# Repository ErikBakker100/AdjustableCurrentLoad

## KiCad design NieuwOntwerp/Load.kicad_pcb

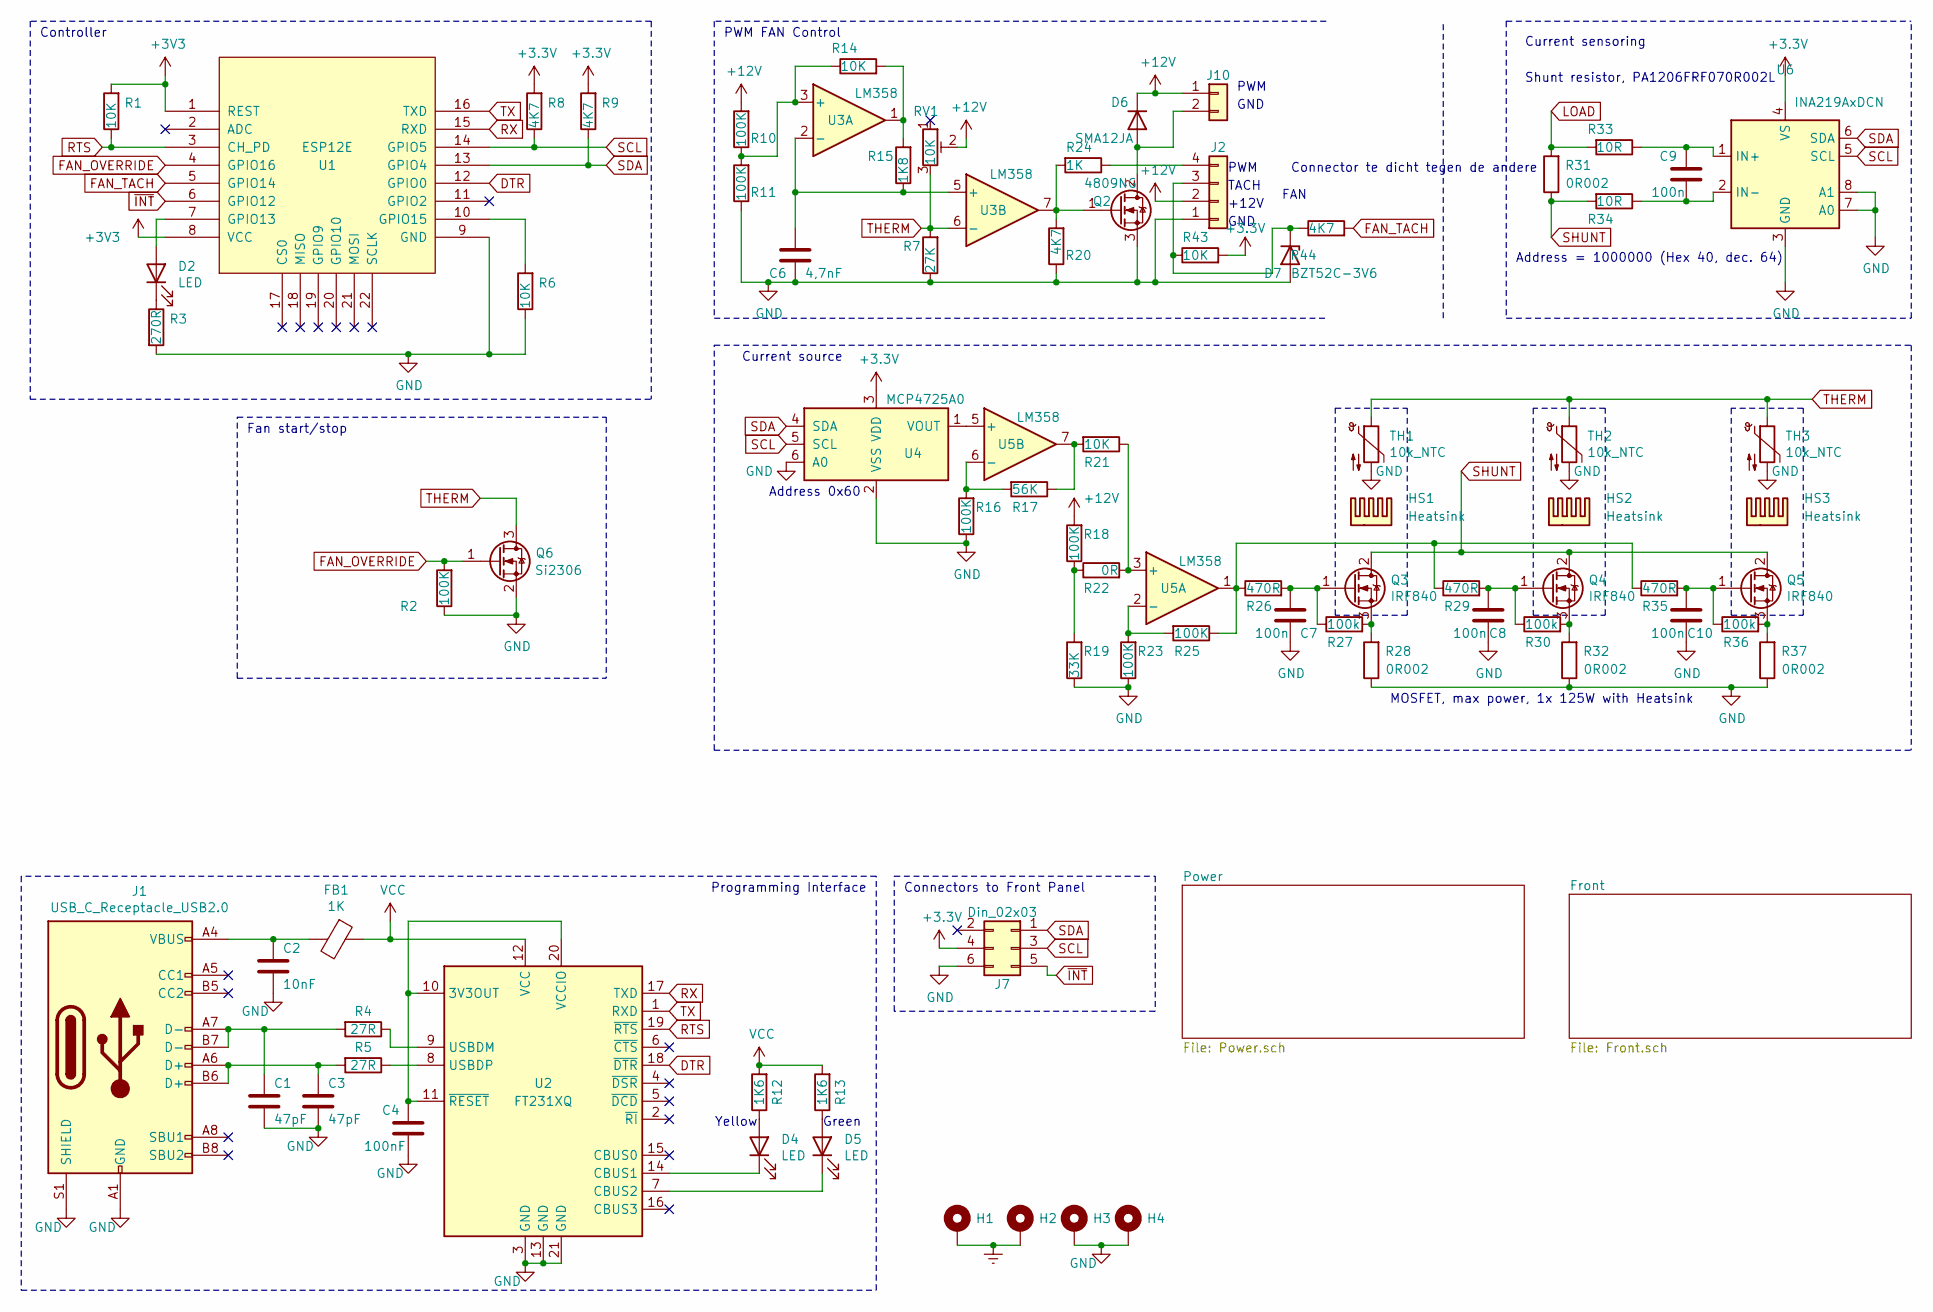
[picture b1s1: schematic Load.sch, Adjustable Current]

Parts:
C1, C3: 47pF; C_0402_1005Metric
C2: 10nF; C_0402_1005Metric
C4: 100nF; C_0603_1608Metric
C6: 4,7nF; C_0402_1005Metric
C7, C8, C9, C10: 100n; C_0603_1608Metric
D2: LED; LED_0603_1608Metric_Pad1.05x0.95mm_HandSolder
D4, D5: LED; LED_0603_1608Metric
D6: SMA12JA; D_SMA
D7: BZT52C-3V6; D_SOD-123
FB1: 1K; R_0603_1608Metric
H1, H2, H3, H4: MountingHole_Pad; MountingHole_3.2mm_M3_DIN965_Pad
HS1, HS2, HS3: Heatsink; Heatsink_TO220
J1: USB_C_Receptacle_USB2.0; USB-C_Receptable_SMD_16pin
J2: Conn_01x02; JST_XH_B4B-XH-A_1x04_P2.50mm_Vertical
J7: Din_02x03; IDC-Header_2x03_P2.54mm_Vertical
J10: Conn_01x02; JST_XH_B2B-XH-AM_1x02_P2.50mm_Vertical
Q2: 4809NG; 369AA
Q3, Q4, Q5: IRF840; TO-220-3_Vertical
Q6: Si2306; SOT-23
R1, R6, R14, R21, R43: 10K; R_0603_1608Metric
R2, R10, R11, R16, R18, R23, R25: 100K; R_0603_1608Metric
R3: 270R; R_0603_1608Metric
R4, R5: 27R; R_0402_1005Metric
R7: 27K; R_0603_1608Metric
R8, R9, R20, R44: 4K7; R_0603_1608Metric
R12, R13: 1K6; R_0603_1608Metric
R15: 1K8; R_0603_1608Metric
R17: 56K; R_0603_1608Metric
R19: 33K; R_0603_1608Metric
R22: 0R; R_0603_1608Metric
R24: 1K; R_0603_1608Metric
R26, R29, R35: 470R; R_0603_1608Metric
R27, R30, R36: 100k; R_0603_1608Metric
R28, R31, R32, R37: 0R002; R_1206_3216Metric
R33, R34: 10R; R_0603_1608Metric
RV1: 10K; Potentiometer_Bourns_3296W_Vertical
TH1, TH2, TH3: 10k_NTC; THERM_NXRT15XH103FA1B040
U1: ESP12E; ESP-12E_SMD
U2: FT231XQ; QFN-20-1EP_4x4mm_P0.5mm_EP2.5x2.5mm
U3, U5: LM358; SOIC-8_3.9x4.9mm_P1.27mm
U4: MCP4725A0; SOT-23-6
U6: INA219AxDCN; SOT-23-8

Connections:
+12V: D6.1 (K), J2.2, J10.1, R10.2, R18.2, RV1.2; also elsewhere on the board
DTR: U1.12 (GPIO0), U2.18 (~DTR)
Earth: H1.1, H2.1; also elsewhere on the board
FAN_OVERRIDE: Q6.1 (G), R2.2, U1.4 (GPIO16)
FAN_TACH: R44.2, U1.5 (GPIO14)
GND: C1.2, C2.2, C3.2, C4.2, C6.1, C7.1, C8.1, C10.1, D7.2 (A), H3.1, H4.1, J1.A1 (GND), J1.A12 (GND), J1.B1 (GND), J1.B12 (GND), J1.S1 (SHIELD), J2.1, J7.6, Q2.3 (S), Q6.2 (S), R2.1, R3.2, R6.1, R7.1, R11.1, R16.1, R19.1, R20.1, R23.1, R28.1, R32.1, R37.1, TH1.2, TH2.2, TH3.2, U1.9 (GND), U2.3 (GND), U2.13 (GND), U2.21 (GND), U4.2 (VSS), U4.6 (A0), U6.3 (GND), U6.7 (A0), U6.8 (A1); also elsewhere on the board
LOAD: R31.2, R33.2; also elsewhere on the board
unnamed: C1.1, J1.A7 (D-), J1.B7 (D-), R4.2
unnamed: C2.1, FB1.2, J1.A4 (VBUS), J1.A9 (VBUS), J1.B4 (VBUS), J1.B9 (VBUS)
unnamed: C3.1, J1.A6 (D+), J1.B6 (D+), R5.2
unnamed: C4.1, U2.10 (3V3OUT), U2.11 (~RESET), U2.20 (VCCIO)
unnamed: C6.2, R15.1, U3.2 (-), U3.5 (+)
unnamed: C7.2, Q3.1 (G), R26.2, R27.1
unnamed: C8.2, Q4.1 (G), R29.2, R30.1
unnamed: C9.1, R33.1, U6.1 (IN+)
unnamed: C9.2, R34.1, U6.2 (IN-)
unnamed: C10.2, Q5.1 (G), R35.2, R36.1
unnamed: D2.1 (K), R3.1
unnamed: D2.2 (A), U1.7 (GPIO13)
unnamed: D4.1 (K), U2.14 (CBUS1)
unnamed: D4.2 (A), R12.1
unnamed: D5.1 (K), U2.7 (CBUS2)
unnamed: D5.2 (A), R13.1
unnamed: D6.2 (A), J10.2, Q2.2 (D)
unnamed: D7.1 (K), J2.3, R43.1, R44.1
unnamed: J2.4, R24.1
unnamed: Q2.1 (G), R20.2, R24.2, U3.7
unnamed: Q3.3 (S), R27.2, R28.2
unnamed: Q4.3 (S), R30.2, R32.2
unnamed: Q5.3 (S), R36.2, R37.2
unnamed: R4.1, U2.9 (USBDM)
unnamed: R5.1, U2.8 (USBDP)
unnamed: R6.2, U1.10 (GPIO15)
unnamed: R10.1, R11.2, R14.1, U3.3 (+)
unnamed: R14.2, R15.2, U3.1
unnamed: R16.2, R17.2, U5.6 (-)
unnamed: R17.1, R21.2, U5.7
unnamed: R18.1, R19.2, R22.1
unnamed: R21.1, R22.2, U5.3 (+)
unnamed: R23.2, R25.2, U5.2 (-)
unnamed: R25.1, R26.1, R29.1, R35.1, U5.1
unnamed: U4.1 (VOUT), U5.5 (+)
RTS: R1.1, U1.3 (CH_PD), U2.19 (~RTS)
RX: U1.15 (RXD), U2.17 (TXD)
SCL: J7.3, R8.1, U1.14 (GPIO5), U4.5 (SCL), U6.5 (SCL)
SDA: J7.1, R9.1, U1.13 (GPIO4), U4.4 (SDA), U6.6 (SDA)
SHUNT: Q3.2 (D), Q4.2 (D), Q5.2 (D), R31.1, R34.2
THERM: Q6.3 (D), R7.2, RV1.3, TH1.1, TH2.1, TH3.1, U3.6 (-)
TX: U1.16 (TXD), U2.1 (RXD)
VCC: FB1.1, R12.2, R13.2, U2.12 (VCC); also elsewhere on the board
~INT: J7.5, U1.6 (GPIO12)

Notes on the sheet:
Address = 1000000 (Hex 40, dec. 64)
Shunt resistor, PA1206FRF070R002L
Current sensoring
MOSFET, max power, 1x 125W with Heatsink
Current source
Controller
Address 0x60
Yellow
Green
Programming Interface
FAN
GND
+12V
TACH
PWM
PWM FAN Control
Fan start/stop
Connectors to Front Panel
Connector te dicht tegen de andere

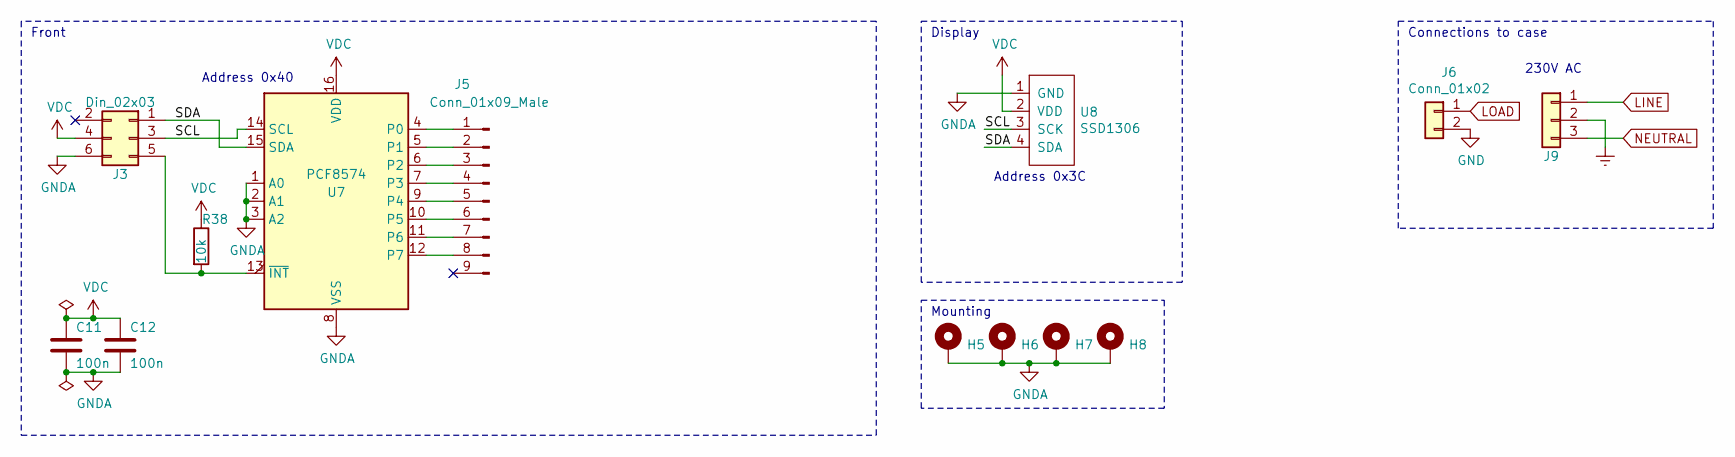
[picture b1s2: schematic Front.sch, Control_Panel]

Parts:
C11, C12: 100n; C_0603_1608Metric
H5, H6, H7, H8: MountingHole_Pad; MountingHole_3.2mm_M3_Pad
J3: Din_02x03; IDC-Header_2x03_P2.54mm_Vertical
J5: Conn_01x09_Male; PinHeader_1x09_P2.54mm_Vertical
J6: Conn_01x02; JST_XH_B2B-XH-AM_1x02_P2.50mm_Vertical
J9: Conn_01x02; JST_XH_B3B-XH-AM_1x03_P2.50mm_Vertical
R38: 10k; R_0603_1608Metric
U7: PCF8574; SOIC-16W_7.5x10.3mm_P1.27mm
U8: SSD1306

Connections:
/Front/SCL: J3.3, U7.14 (SCL), U8.3 (SCK)
/Front/SDA: J3.1, U7.15 (SDA), U8.4 (SDA)
Earth: J9.2; also elsewhere on the board
GND: J6.2; also elsewhere on the board
GNDA: C11.1, C12.1, H5.1, H6.1, H7.1, H8.1, J3.6, U7.1 (A0), U7.2 (A1), U7.3 (A2), U7.8 (VSS), U8.1 (GND)
LINE: J9.1; also elsewhere on the board
LOAD: J6.1; also elsewhere on the board
NEUTRAL: J9.3; also elsewhere on the board
unnamed: J3.5, R38.2, U7.13 (~INT~)
unnamed: J5.1, U7.4 (P0)
unnamed: J5.2, U7.5 (P1)
unnamed: J5.3, U7.6 (P2)
unnamed: J5.4, U7.7 (P3)
unnamed: J5.5, U7.9 (P4)
unnamed: J5.6, U7.10 (P5)
unnamed: J5.7, U7.11 (P6)
unnamed: J5.8, U7.12 (P7)
VDC: C11.2, C12.2, J3.4, R38.1, U7.16 (VDD), U8.2 (VDD)

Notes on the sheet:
Display
Address 0x3C
Address 0x40
Front
Mounting
230V AC
Connections to case

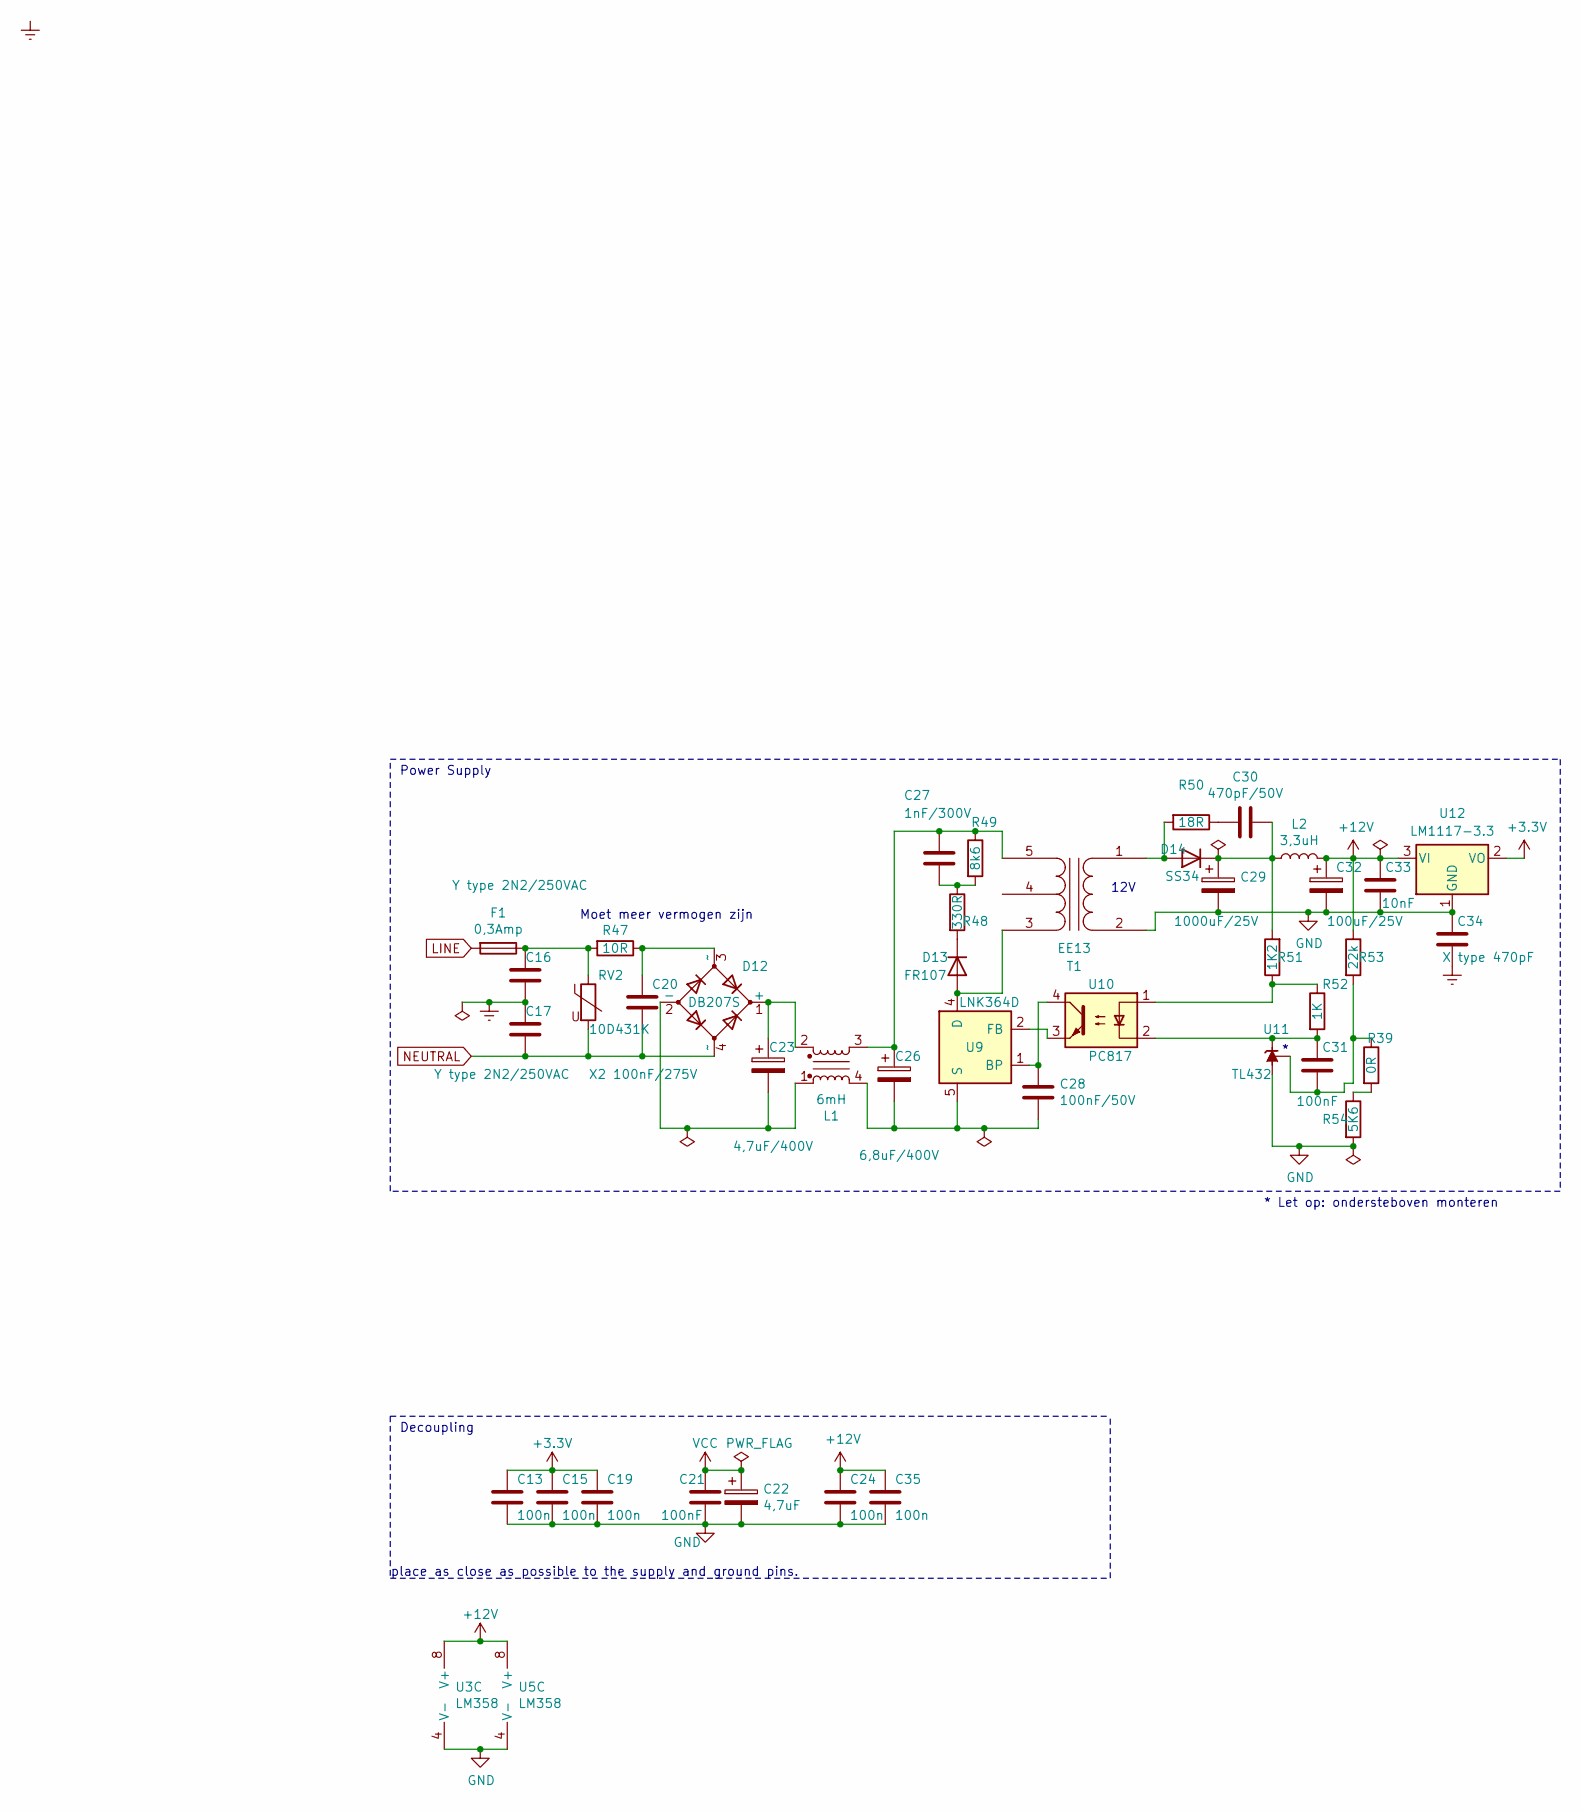
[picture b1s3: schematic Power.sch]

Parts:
C13, C15, C19, C24, C35: 100n; C_0603_1608Metric
C16, C17: Y type 2N2/250VAC; Y2_222
C20: X2 100nF/275V; CBB22104J400V
C21, C31: 100nF; C_0603_1608Metric
C22: 4,7uF; C_Elec_4x5.4
C23: 4,7uF/400V; CP_Radial_D8.0mm_P3.50mm
C26: 6,8uF/400V; CP_Radial_D8.0mm_P3.50mm
C27: 1nF/300V; JN_102M
C28: 100nF/50V; C_0603_1608Metric
C29: 1000uF/25V; CP_Radial_D10.0mm_P5.00mm
C30: 470pF/50V; C_0603_1608Metric
C32: 100uF/25V; CP_Radial_D5.0mm_P2.00mm
C33: 10nF; C_0603_1608Metric
C34: X type 470pF; JN_102M
D12: DB207S; SOT4_Rectifier_Bridge
D13: FR107; D_SMA
D14: SS34; D_SMA
F1: 0,3Amp; fuse-clip-5x20mm
L1: 6mH; UU98_Common_Mode_Choke
L2: 3,3uH; L_1206_3216Metric
R39: 0R; R_0603_1608Metric
R47: 10R; R_Axial_DIN0411_L9.9mm_D3.6mm_P5.08mm_Vertical
R48: 330R; R_Axial_DIN0207_L6.3mm_D2.5mm_P2.54mm_Vertical
R49: 8k6; R_Axial_DIN0207_L6.3mm_D2.5mm_P2.54mm_Vertical
R50: 18R; R_1206_3216Metric
R51: 1K2; R_0603_1608Metric
R52: 1K; R_0603_1608Metric
R53: 22k; R_0402_1005Metric
R54: 5K6; R_0603_1608Metric
RV2: 10D431K; RV_Disc_D10mm_W2mm_P8mm
T1: EE13; EE16-A2
U3, U5: LM358; SOIC-8_3.9x4.9mm_P1.27mm
U9: LNK364D; PowerIntegrations_SO-8C
U10: PC817; SSO-4_6.7x5.1mm_P2.54mm_Clearance8mm
U11: TL432; SOT-23
U12: LM1117-3.3; SOT-223-3_TabPin2

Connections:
+12V: C24.2, C32.1, C33.1, C35.2, L2.2, R53.1, U3.8 (V+), U5.8 (V+), U12.3 (VI); also elsewhere on the board
Earth: C16.1, C17.2, C34.1; also elsewhere on the board
GND: C13.1, C15.1, C19.1, C21.2, C22.2, C24.1, C29.2, C32.2, C33.2, C34.2, C35.1, R54.2, T1.2 (AB), U3.4 (V-), U5.4 (V-), U11.3 (A), U12.1 (GND); also elsewhere on the board
LINE: F1.2; also elsewhere on the board
NEUTRAL: C17.1, C20.2, D12.4 (~~), RV2.2; also elsewhere on the board
unnamed: C16.2, F1.1, R47.2, RV2.1
unnamed: C20.1, D12.3 (~~), R47.1
unnamed: C23.1, D12.1 (+), L1.2
unnamed: C23.2, D12.2 (-), L1.1
unnamed: C26.1, C27.1, L1.3, R49.1, T1.5 (SB)
unnamed: C26.2, C28.2, L1.4, U9.5 (S), U9.6 (S), U9.7 (S), U9.8 (S)
unnamed: C27.2, R48.1, R49.2
unnamed: C28.1, U9.1 (BP), U10.4
unnamed: C29.1, C30.1, D14.1 (K), L2.1, R51.2
unnamed: C30.2, R50.1
unnamed: C31.1, R52.2, U10.2, U11.1 (K)
unnamed: C31.2, R39.1, R53.2, U11.2 (REF)
unnamed: D13.1 (K), R48.2
unnamed: D13.2 (A), T1.3 (SA), U9.4 (D)
unnamed: D14.2 (A), R50.2, T1.1 (AA)
unnamed: R39.2, R54.1
unnamed: R51.1, R52.1, U10.1
unnamed: U9.2 (FB), U10.3
VCC: C21.1, C22.1; also elsewhere on the board

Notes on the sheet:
12V
Power Supply
place as close as possible to the supply and ground pins.
Decoupling
* Let op: ondersteboven monteren
Moet meer vermogen zijn

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
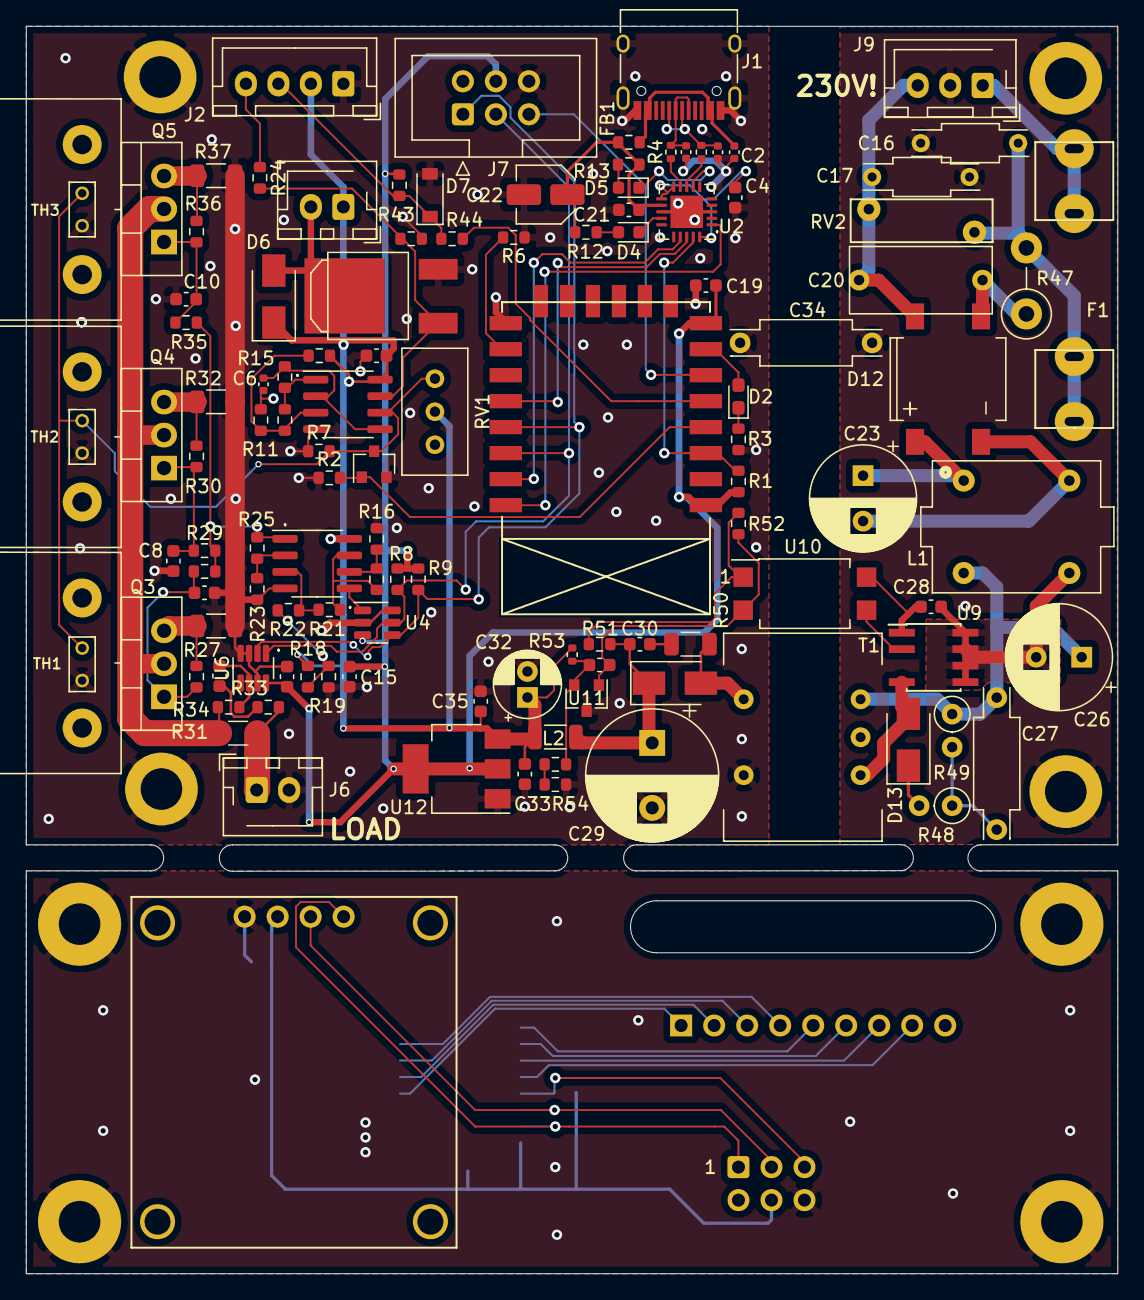
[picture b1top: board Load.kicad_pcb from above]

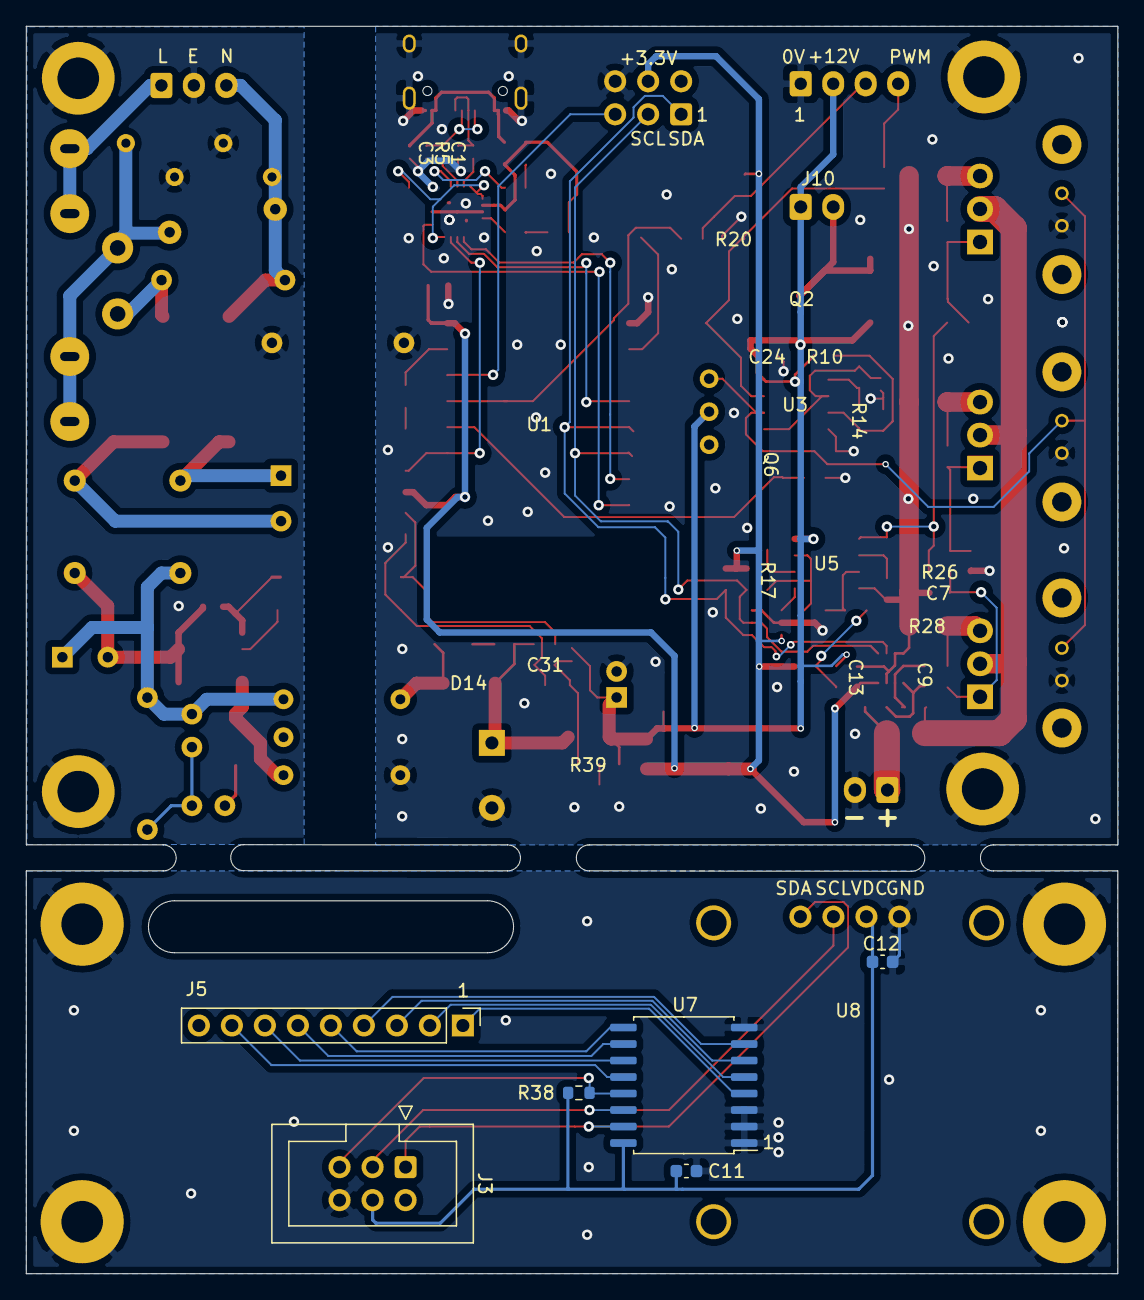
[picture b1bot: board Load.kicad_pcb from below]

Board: 2 copper layers, 84.0 x 96.0 mm, 134 parts (6 on the bottom side), 85 nets.

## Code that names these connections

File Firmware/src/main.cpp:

#include <Wire.h>
#include "I2CKeyPad.h"
#include "tacho.h"
#include "display.h"
#include "MCP4725.h"
#include <Adafruit_INA219.h>

/*
* pin number is equal to GPIO
* pin 1 = GPIO1 = TX
* pin 2 = GPIO2 = D4
* pin 3 = GPIO3 = RX
* pin 4 = GPIO4 = D2
* pin 5 = GPIO5 = D1
* pin 12 = GPIO12 = D6
* pin 13 = GPIO13 = D7
* pin 14 = GPIO14 = D5
* pin 15 = GPIO15 = D8
* pin 16 = GPIO16 = D0
*/

// Set variables of the different devices
const uint8_t PCF8574_Interrupt_Pin{12};
const uint8_t PCF8574_Address{0x20}; 
const uint32_t I2CSPEED{1000000}; // I2C bus speed
const uint8_t FAN_OVERRIDE{16}; // Output which controls the FAN
const uint8_t MCP4725_Address{0x60};
const uint8_t INA219_Address{0x40};
const uint8_t SSD1306_address{0x3c};
const uint8_t tacho_pin{14};
// SSD1306 Display setup
SSD1306Wire display(SSD1306_address, SDA, SCL);

// PCF8574 / keypad setup
I2CKeyPad keyPad(PCF8574_Address);
char keys[] = "147L2580369RUDERNF";  // N = Nokey, F = Fail (eg >1 keys pressed)
volatile bool keyChange = false;  // volatile for IRQ var
bool Keypadconnected{false};
void IRAM_ATTR keyChanged() // we need IRAM_ATTR for interrupt routine on ESP12E
{ keyChange = true; }
bool keypressed{false}; // Set as long as a key is being pressed

// help functions setup
void check_if_exist_I2C();
byte check_if_exist_I2C(uint8_t);
void measurePolling(uint32_t speed);
uint32_t stop{0}; //Used for timing
void WriteINAdata();

// FAN setup
tacho FanSpeed(tacho_pin);

// D/A converter (MCP4725) setup
MCP4725 MCP(MCP4725_Address);
bool MCP4725connected{false};
uint16_t output_value{0}; // the output level between - 4096, determines the load
// INA219 Current sensor setup
Adafruit_INA219 ina219;
bool INA219connected{false};

void setup()
{
  Serial.begin(115200);
  delay(200);
  Serial.print("Initializing ");
  Serial.println(__FILE__);
  pinMode(LED_BUILTIN, OUTPUT);
  pinMode(FAN_OVERRIDE, OUTPUT);
  digitalWrite(FAN_OVERRIDE, LOW); // timer gebruiken om na opstarten de FAN eventjes maximaal te laten draaien

  // NOTE: PCF8574 will generate an interrupt on key press and release.
  attachInterrupt(digitalPinToInterrupt(PCF8574_Interrupt_Pin), keyChanged, FALLING);
  keyChange = false;

  Wire.begin();
  Wire.setClock(I2CSPEED);
  check_if_exist_I2C();
// Initialize the display
  if (!check_if_exist_I2C(SSD1306_address)) {
    display.init();
    display.resetDisplay();
    display.flipScreenVertically();
    display.displayOn();
    display.clear();
    display.drawString(1, 1, "Start");
    display.display();
  }

  if (keyPad.begin() == false)
  {
    Serial.print("Could not find keypad.\r\n");
  } else {
    Keypadconnected = true;
    Serial.print("Keypad OK.\r\n");
    }
  if (Keypadconnected) measurePolling(I2CSPEED);
  
  if (MCP.begin() == false)
  {
    outputinfo("Could not find D/A\r\n", &display);
  } else {
    MCP4725connected = true;
    MCP.setValue(output_value);
    outputinfo("D/A converter OK.\r\n", &display);
  }
  // Initialize the INA219.
  // By default the initialization will use the largest range (32V, 2A).  However you can call a setCalibration function to change this range (see comments).
  if (ina219.begin() == false) {
    outputinfo("Could not find Current sensor\r\n", &display);
  } else { 
    INA219connected = true;
    //ina219.setCalibration_32V_1A(); // To use a slightly lower 32V, 1A range (higher precision on amps)
    //ina219.setCalibration_16V_400mA(); // Or to use a lower 16V, 400mA range (higher precision on volts and amps):
    outputinfo("Current sensor OK.\r\n", &display);
  }
  Serial.print("Init finalised\r\n");
}

void loop()
{
   if(Keypadconnected) {
    if (keyChange)
    {
      keypressed = true;
      uint8_t idx = keyPad.getKey();
      // only after keychange is handled it is time to reset the flag
      keyChange = false;
      if (idx != 16)
      {
        if (keys[idx] == 'U') {
          if (MCP4725connected) {
            output_value += 10;
            output_value &= 0x0FFF;
            MCP.setValue(output_value);
          }
        }
        if (keys[idx] == 'D') {
          if (MCP4725connected) {
            output_value -= 10;
            output_value &= 0x0FFF;
            MCP.setValue(output_value);
          }
        }
      } else {
        Serial.print("release\r\n");
        keypressed = false;
      }
      Serial.printf("Key %c, output_value %d\r\n", keys[idx], output_value);
    }
  }
  //INA29 Test
  if (INA219connected) {
    if(millis()-stop > 500) {
      stop = millis();
      WriteINAdata();
    }
  }
}

void WriteINAdata() {
  float Voltage = ina219.getBusVoltage_V();
  float Current = ina219.getCurrent_mA();
  float Power = ina219.getPower_mW();
  int16_t Fan = FanSpeed.rpm();
  if (!check_if_exist_I2C(SSD1306_address)) {
    char buffer[40];
    display.clear();
    display.drawStringf(0, 0, buffer, "Voltage: %.2f V", Voltage);
    display.drawStringf(0, 10, buffer, "Current: %.2f mA", Current);
    display.drawStringf(0, 20, buffer, "Power: %.2f mW", Power);
    display.drawStringf(0, 30, buffer, "Fan: %d rpm", Fan);
    display.display();
  }
  Serial.printf("Voltage: %.2f V\r\n", Voltage);
  Serial.printf("Current: %.2f mA", Current);
  Serial.printf("Power: %.2f mW", Power);
  Serial.printf("Fan: %lf rpm, Fan\r\n", Voltage);
}

void measurePolling(uint32_t speed)
{
  Serial.print("Measuring time to scan the keypad in micro seconds\r\n");
  Serial.print("Freq \tkey \ttime\r\n");
  // measure time to check isPressed() by polling.

  //  CLOCK      TIME (us)
  //  ---------------------
  //  100K       570
  //  200K       276
  //  300K       171
  //  400K       132
  //  500K       128
  //  600K       132
  //  700K       128
  //  800K       132
  //  900K       128
  //  1M         132
  
  for (uint32_t clock = 100000; clock <= 1000000; clock += 100000)
  {
    Wire.setClock(clock);
    // reference time for keyPressed check UNO ~
    uint32_t start = micros();
    uint8_t idx = keyPad.isPressed();
    uint32_t stop = micros();
    Serial.print(String(clock));
    Serial.print("\t");
    Serial.print(String(idx));
    Serial.print("\t");
    Serial.print(String(stop - start)+"\r\n");
    delay(10);
  }
  Wire.setClock(I2CSPEED);
}


void check_if_exist_I2C() {
  byte error, address;
  int nDevices {0};
  Serial.print("Device(s) found at address(es) : \r\n");
  for (address = 1; address < 127; address++ )  {
    error = check_if_exist_I2C(address);
    char hexdecimalnum [4]{0,0,0,0};
    itoa(address, hexdecimalnum, 16);
    if (error == 0){
      Serial.print(String(hexdecimalnum) + "\r\n");
      nDevices++;
    } else if (error == 4) {
      Serial.print("Unknow error at address 0x");
      Serial.print(String(hexdecimalnum) + "\r\n");
    }
  } //for loop
  if (nDevices == 0) Serial.print("No I2C devices found\r\n");
}

byte check_if_exist_I2C(uint8_t address) {
    // The i2c_scanner uses the return value of
    // the Write.endTransmisstion to see if
    // a device did acknowledge to the address.
    Wire.beginTransmission(address);
    return Wire.endTransmission();
}
// -- END OF FILE --

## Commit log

2021-01-31 31-1-2021
2021-04-04 4-4-2021
2021-04-27 Sync_21-04-27
2021-04-27 2021-04-27_02
2021-05-13 2021-05-13_01
2021-05-14 2021-05-14_01
2021-05-14 2021-05-14_02
2021-05-15 2021-05-15_01
2021-05-15 2021-05-15_02
2021-05-16 2021-05-16_01
2021-09-12 start
2021-09-13 Keyboard
2021-09-14 Keypad
2021-09-14 KeypadTestVersion
2021-09-19 Keypad OK
2021-09-19 MCP4725 BEGIN
2021-09-20 INA Begin
2021-10-22 Print_update
2021-10-23 print update
2021-10-24 Print gereed
2021-11-21 21-11-2021
